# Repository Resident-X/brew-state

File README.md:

# `brew-state` — a model-based controller for a dual-thermoblock espresso machine

Replacing the factory control board in a Sunbeam EM7000 with a controller that actually models the machine: state estimation, a forward horizon, flow and pressure profiling, and a hardware safety chain with no firmware anywhere in it.

This repository is **public domain**. Take any of it.

## How this project is built

Requirements first, then code. The `specs/` graph is finished before firmware starts, and this repo is partly an argument that working in that order is faster rather than slower.

That means the graph is the substance here, and anything under `specs/` describes the machine as it is meant to be — not as it currently is.

## Where to start reading

**If you want to know what this machine is meant to do**, read the personas and journeys first. They are written to be read by a person, not parsed by a tool:

- `specs/personas/` — three stakeholders. The **operator** who makes coffee, the **builder** who designs and commissions it, and the **adopter** who found this published and owns a different machine.
- `specs/journeys/` — what actually happens: pulling a shot, steaming a jug, serving a group, commissioning the plant, correcting drift, keeping the machine in condition.

**If you want to know what constrains it**, read `specs/obligations/`. These are the cross-cutting commitments — electrical and thermal safety, real-time discipline, control-design discipline, verification discipline, open-source maintainability, physical configuration control. The safety obligation is the only one whose authority is external to this project, and it outranks everything else in the graph.

**If you want the detail**, `specs/requirements/` holds the functional and constraint requirements, `specs/definitions/` the vocabulary, and `specs/decisions/` the choices that have been made and why — including the options that were rejected.

**If you are rebuilding this on your own machine**, read [`docs/sunbeam-em7000/reference-machine.md`](docs/sunbeam-em7000/reference-machine.md) first. Everything specific to *our* machine — supply voltage, mains frequency, element ratings, protection trip points — lives in that one file. The requirement graph is written without those values so that replacing that file is the whole job.

## Two different promises

Be clear about which of these you are:

- **Same architecture** (a dual-thermoblock machine): the graph should apply to you, and adapting it should mean supplying your own parameters rather than changing requirements.
- **Different architecture** (single boiler, heat exchanger): the requirements will not all fit — an HX group's temperature depends on time since the last shot, which has no representation in a thermoblock's state at any parameter values. What transfers is the **method**, the tooling and the safety architecture. That is a smaller promise, and it is the honest one.

## Reading the graph

Nodes are `.req.yaml` files — plain YAML with prose in them. Reading needs nothing but a text editor. **Changing them is a different matter, and is covered below.**

**How they connect.** A requirement `derives-from` one or more *criteria* of the node above it, so the chain runs persona → journey → requirement, with each node carrying numbered criteria (`REQ-BREW-TEMP-001.C1`) attached by `criterion-of`. Obligations sit across the top: they are not part of that chain but constrain everything under them, and the safety obligation outranks the lot. Requirements also derive from each other's criteria where one genuinely builds on another. Decisions attach by `addresses`.

**Priorities.** Every requirement carries one:

| | |
|---|---|
| `must` | the system is wrong without it |
| `should` | real value, deliberately ranked below the musts |
| `could` | worth having, and shipping without it is not a defect |

Priority is about whether the system is wrong, not about when something gets built.

## Changing the graph

**Do not hand-edit `.req.yaml` files.** The graph is maintained by [Staircase](#staircase), and the engine is what holds it together: it assigns IDs, places files, wires and validates links, enforces the boundary between the requirement and delivery chains, applies the authoring discipline, and records who changed what and when.

Editing a node by hand bypasses all of that, and the failure mode is quiet. The file still parses. What breaks is underneath — a link pointing at something that no longer exists, a criterion orphaned from its parent, a requirement deriving from a retired one, a change landing with no version behind it and no event recording it. Structural validation does not catch most of that, because nothing is malformed. It is simply wrong, and it stays wrong until something downstream fails for reasons that no longer look connected.

That is the whole reason the engine exists. It is not a formatter over some YAML — it is the thing that knows how a systems and delivery graph has to hold together, so that a person changing one node does not have to.

**A caveat you should know before relying on this.** The engine is not part of this repository and is not currently something you can obtain. So you can read everything here, and you can build from it, but you cannot presently maintain a fork of the graph the way it is meant to be maintained. That is a real limit on what this repo currently offers, and it is tracked in the graph itself rather than hidden — `REQ-PUBLISHED-BUILD-PATH-001` requires every tool the path depends on to be obtainable by someone who is not the author, and that criterion is not met today.

## Staircase

This project is built with Staircase, whose thesis is that disciplined, requirement-driven, complete-the-first-time engineering produces better software, faster, that stays maintainable. This repo is partly a test of that claim in public, on a real physical thing that can burn someone.

One discipline is worth knowing about while reading: **requirements state properties, not mechanisms.** You will not find part numbers, sensor technologies, interface choices or tuning constants in `specs/`. Those are decisions and they live separately. That is also what makes the graph portable to a machine on a different continent running on a different voltage — a requirement that names a mechanism does not travel.

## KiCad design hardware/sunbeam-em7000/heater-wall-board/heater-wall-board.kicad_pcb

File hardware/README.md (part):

# Hardware

Board designs and the check every one of them has to pass before it is ordered.

- `hardware/<machine>/` holds one machine's board designs, one KiCad project per board in its own folder, and the `separation-basis.yaml`, `pin-allocation.yaml`, `controller-part.yaml`, `parts-specification.yaml`, `catalogue-extract.yaml` and `board-rules.yaml` they are held to, and the `derating-policy.yaml`, `pin-limits.yaml`, `workmanship-acceptance.yaml` and `severity-policy.yaml` they are held to where a design's folders hold them.
- `hardware/tools/` holds the pre-order check, the locked-copper check used around routing, the layout tools (the mains-copper compare beside it, the safe zone refill, the fill difference, the chain runner and the footprint audit), the command that renders a board's layout review views, the command that renders a placed board's placement view and measures it, the command that seeds the layout review's proof design, the review kit (the command that runs a declared judged review as forks of one shared context), the layout review's caller for it, the command that writes a committed board's review folder, the critical-routing check's caller and the catalogue helpers it shares with the layout caller, the production-files check's caller and the command that writes a real order's review folder, the schematic review's caller, the command that writes a committed schematic's review folder and the command that proves the fanned-out schematic review (with the proof harness it shares with the layout review's), the command that proves the fanned-out layout review, the commands that convert and draw a board's production files and the command that seeds the proof design's production files, and their tests. They work for any machine.
- `hardware/proof/` holds designs committed only to prove the board tooling and the layout review: `gate-proof` for the pre-order check's rules, `record-keys-proof` for the keys its records carry, `review-proof` for the layout review and the ordering step's production-files check, and `circuit-review-proof` for the schematic review. They are never ordered.

A **board design** is a KiCad project file (`.kicad_pro`) together with the schematic (`.kicad_sch`) and layout (`.kicad_pcb`) of the same name beside it. The check finds every design git tracks, wherever it sits. The layout above is a convention for readers, not something the check depends on. A design is checked once git tracks it: `git add` is enough for the design's own files. The check reads a design only as the repository holds it. KiCad is given a copy of the tracked files alone, each in its place in the repository: everything in the design's folder, every sheet its schematic reaches, and every library its `sym-lib-table` and `fp-lib-table` name, wherever in the repository they sit. A library, sheet or rules file left uncommitted is therefore not used. A sheet the schematic names, a custom rules file or library table beside the project, or a library a table names, that git does not track fails the design by name. So does a library the repository cannot hold at all: one named by an absolute path, one outside the repository, or one reached through a path variable other than `${KIPRJMOD}` and those naming the libraries KiCad installs with itself (`${KICAD10_SYMBOL_DIR}`, `${KICAD10_FOOTPRINT_DIR}` and the like). Name a library from its table as `${KIPRJMOD}/` followed by its path from the design's folder. The separation basis record has to be committed exactly as it stands (see below).

KiCad is run with a configuration the check makes for the run, not the one on the machine running it. That configuration names only the libraries KiCad installs with itself, and no `KICAD…` variable from the environment reaches KiCad. A symbol or footprint whose library only one machine's own KiCad setup names, in its global library tables or its path variables, is therefore reported by KiCad as a library its configuration does not include, and fails the design under `design_library`. Put such a library in the repository and name it in the design's own table.

One KiCad run may take at most 7200 s. The limit is the constant `KICAD_TIMEOUT_S` in `hardware/tools/board_check.py`, and `hardware/tools/board_views.py` reads the same constant, so neither tool has a figure of its own. A run that outlives it fails the design as "KiCad did not finish within 7200 s", with the limit in force named, in the check and in the views command; the wait is finite, so a hung run still fails. The figure rests on a measurement made on 2026-10-31 on the main board with its ground and neutral pours and slots: KiCad's creepage test alone took about 10 minutes and the full design check 20 to 30 minutes; a later measurement on the main board as it was laid out found one full-board KiCad pass taking about 50 minutes, nearly all of it the creepage test against the ground pours, and the check makes that pass once (the mounting-hole and sensing passes hold no creepage constraint). 7200 s is about four times the slowest of the first measurements and more than twice the single pass measured later, the margin that lets a slower machine or a denser board finish.

## What you need

Every tool is free. The check stops with an error naming any tool that is missing or too old, rather than skipping the checks that need it.

| Tool | Minimum | Where to get it |
|---|---|---|
| KiCad (its `kicad-cli`) | KiCad 10.0 | https://www.kicad.org/download/. This repository's board files are in KiCad 10's format, which older versions cannot open. |
| Python | Python 3.9 | https://www.python.org/downloads/ |
| PyYAML | PyYAML 5.1 | `pip install pyyaml`, or your system's `python3-yaml` package |
| git | git 2.11 | https://git-scm.com/downloads |
| Task | 3 | https://taskfile.dev/installation/ |
| resvg, for the layout review views and for the tooling tests the build round runs | resvg 0.47 | A prebuilt program from https://github.com/linebender/resvg/releases: the v0.47.0 release carries one for each of Windows (`resvg-win64.zip`), macOS and Linux (x86_64), and later releases carry them for macOS and Linux only. Or `brew install resvg` with Homebrew, on macOS or Linux. Or `cargo install resvg` with a Rust toolchain from https://rustup.rs/, on any operating system. It turns the views into images. The pre-order check itself does not need it, but the tooling tests that the build round and the nightly run draw views, so those need it too ([When the board check runs](#when-the-board-check-runs)). |
| gerbonara, for the commands that draw a board's exported fabrication layers and for the tooling tests the build round runs | gerbonara 1.6.3, exactly | A Python library under the Apache licence, https://pypi.org/project/gerbonara/. Install it into a virtual environment of its own with `task hw:gerbonara`, which makes one in your user cache folder (`GERBONARA_VENV` puts it elsewhere), or by hand with `python3 -m venv <folder>` then `<folder>/bin/python -m pip install gerbonara==1.6.3` (on Windows `<folder>\Scripts\python.exe`) and name that environment's Python as `GERBONARA_PYTHON`. It reads the Gerber and drill files KiCad exports, which `kicad-cli` cannot, and the ordering step of the method turns each into a vector image that resvg rasterises. The pre-order check itself does not need it, but the tooling tests that the build round and the nightly run draw layers from exported files, so those need it too. A command or a test that needs it and does not find that version stops with `CANNOT RUN` naming it. |
| KiCad's own Python, for the layout tools that run KiCad's scripting interface (the zone refill, the fill difference and any chain step that loads a board) | the interpreter that ships with KiCad 10.0 | It is part of the KiCad install: the one interpreter that can `import pcbnew`. Name it with the environment variable `KICAD_PYTHON`, or with the tool's `--kicad-python` argument, which wins. A tool and its tests that need it stop with `CANNOT RUN` naming `KICAD_PYTHON` when it is unset or names nothing runnable. Check it with `"$KICAD_PYTHON" -c "import pcbnew; print(pcbnew.Version())"`. Its usual location is in the table below. `task hw:test` and `task hw:test:round` find it as they find `KICAD_CLI`: the variable when set, else the macOS install's interpreter when it is there, else the system `python3` when that can import `pcbnew`, else nothing, and the tests that need it stop naming it. The nightly verification's runner sets it, and `KICAD_FOOTPRINTS`, in a step that fails the provisioning when `/usr/bin/python3` cannot import `pcbnew`. |
| numpy, shapely, Pillow and PyYAML, for the silkscreen command (`silkscreen.py build`, `check` and `prove`) and the tests of it | numpy 2.5.0, shapely 2.2.0, Pillow 12.3.0 and PyYAML 6.0.3, or later | Python libraries. Install them into a virtual environment of their own with `task hw:silkscreen`, which makes one in your user cache folder (`SILKSCREEN_VENV` puts it elsewhere), or into the Python that runs the command by hand (`pip install numpy shapely Pillow pyyaml`, or your system's `python3-numpy`, `python3-shapely`, `python3-pil` and `python3-yaml` packages). The rest of the board tooling does not need them, and no tool here carries a copy of them. A command or test that needs one and does not find it stops with `CANNOT RUN` naming the package. |
| A monospaced font for the captions, for the layout review views and for the tooling tests the build round runs | DejaVu Sans Mono, or Menlo, Consolas, Liberation Mono or Courier New | The captions are drawn in the first of these that resvg finds among the system's fonts. macOS carries Menlo and Windows carries Consolas. Elsewhere, install DejaVu Sans Mono from https://dejavu-fonts.github.io/ or your system's package of it (for example `fonts-dejavu`). Without one the command, or the tooling tests, stop with `CANNOT RUN`. |

`kicad-cli` is often installed off the search path. The tasks use the variable `KICAD_CLI`, which defaults to the bare name `kicad-cli`. If it is not on your search path, set the variable to the tool's full path, either on the command line (`task hw:verify KICAD_CLI=/path/to/kicad-cli`) or in the environment. Its usual location:

| System | `kicad-cli` |
|---|---|
| macOS | `/Applications/KiCad/KiCad.app/Contents/MacOS/kicad-cli` |
| Windows | `C:\Program Files\KiCad\10.0\bin\kicad-cli.exe` |
| Linux (distribution or PPA package) | `/usr/bin/kicad-cli` |
| Linux (Flatpak) | not a file on the path: write a one-line script that runs `flatpak run --command=kicad-cli org.kicad.KiCad "$@"` and point `KICAD_CLI` at it |

KiCad's stock footprint libraries are needed by the main board's layout chain only when a block must take a part from them that the board does not carry (a part swap or a clamp it adds); the chain stops with `KICAD_FOOTPRINTS must name KiCad's stock footprint libraries ...` naming the variable when that happens and the variable is unset or names no folder. Name the folder that holds `Capacitor_SMD.pretty` and the other `.pretty` folders with `KICAD_FOOTPRINTS`: on macOS `/Applications/KiCad/KiCad.app/Contents/SharedSupport/footprints`, on Windows `C:\Program Files\KiCad\10.0\share\kicad\footprints`, on Linux `/usr/share/kicad/footprints`. Running the chain over the committed main board needs no part from them. The same two tasks pass `KICAD_FOOTPRINTS` on, taking the variable when set and else the first of the macOS and Linux places above that exists.

KiCad's own Python is, on each system, usually:

| System | `KICAD_PYTHON` |
|---|---|
| macOS | `/Applications/KiCad/KiCad.app/Contents/Frameworks/Python.framework/Versions/Current/bin/python3` |
| Windows | `C:\Program Files\KiCad\10.0\bin\python.exe` |
| Linux (distribution or PPA package) | `/usr/bin/python3`, which imports `pcbnew` once the `kicad` package is installed |
| Linux (Flatpak) | not a file on the path: write a one-line script that runs `flatpak run --command=python3 org.kicad.KiCad "$@"` and point `KICAD_PYTHON` at it |

`SILKSCREEN_PYTHON` is the Python of the silkscreen libraries' environment (`task hw:silkscreen`, pinned to numpy 2.5.0, shapely 2.2.0, Pillow 12.3.0 and PyYAML 6.0.3, which the command's table needs, safe to run again). It defaults to the Python of that environment once it exists and to `python3` when there is none. The silkscreen command and its tests start in whatever Python runs them; when that lacks one of the three packages and `SILKSCREEN_PYTHON` names a Python that has all three, they run again under it, so a bare `python3` works. When neither has them, the command stops with `CANNOT RUN` naming the missing package, the task and the variable. `task hw:test` and `task hw:test:round` pass the variable to the tests, and the nightly run installs the same pinned versions into its own environment and sets it.

`GERBONARA_PYTHON` is the Python of the virtual environment above. The tasks that draw layers use the variable, which defaults to the Python of the environment `task hw:gerbonara` makes and to `python3` when there is none, so only an environment made by hand needs it set, on the command line (`task hw:production-seed GERBONARA_PYTHON=/path/to/venv/bin/python -- ...`) or in the environment.

`resvg` is one program, wherever it was unpacked. The view tasks use the variable `RESVG`, which defaults to the bare name `resvg`. If it is not on your search path, set it to the program's full path, for example `task hw:views RESVG=/path/to/resvg -- ...`.

## The commands

- `task hw:verify` runs the pre-order check on every board design in the repository. It exits 0 only when every design passes. A build round runs it for a change that can matter to a board, and the nightly run of `main` runs it every night ([When the board check runs](#when-the-board-check-runs)).
- `task hw:prove` seeds each fault the check guards against into a throwaway copy of `hardware/proof/gate-proof` (or, for a fault about the keys of a record, of `hardware/proof/record-keys-proof`, for a fault about an unlisted pin of `hardware/proof/circuit-review-proof`, and for a fault about sensing clearance or ground returns of `hardware/proof/review-proof`) as the last commit holds it, in a temporary directory outside the repository, so an uncommitted edit to the proof design is not what it proves. It requires the check to catch each fault. This command is on demand: neither the build round nor the nightly runs it.
- `task hw:review-seed -- --seeds <file> --out <folder>` seeds known layout defects into a throwaway copy of `hardware/proof/review-proof` and writes a folder to review it blind, with the seed list apart (see [The proof designs](#the-proof-designs)). This command is on demand and is not part of the gate. It needs the same tools as `hw:views`.
- `task hw:production-review-folder -- --repo <repository> --commit <commit> --design <board folder> --out <folder> --work <folder> --views <folder> --placement <folder> --preview <folder> --preview-note <text> --tools <text> --command <text> ...` writes the review folder of a real order's production-files check for a judged review to read ([The production-files check by unit](#the-production-files-check-by-unit)). This command is on demand and is not part of the gate. It needs git and Python, no KiCad and no gerbonara.
- `task hw:production-seed -- --seeds <file> --out <folder>` seeds known defects into the production files of `hardware/proof/review-proof` and writes a folder to check them blind, with the seed list apart (see [The proof designs](#the-proof-designs)). This command is on demand and is not part of the gate. It needs the same tools as `hw:views`, and gerbonara.
- `task hw:test` runs the tests of the check itself, of the locked-copper check's four commands, of the layout review views, of the placement view, of the placement and critical routing history check, of the layout review record history check, of the layout review proof's seeding command, of the schematic sheet drawing command, of the review kit (its session specification and executors, answer reading, stream checks and telemetry, declaration, catalogue and shared context, planner and scheduler, merge and replicas, caller contract, contract smoke, the command and the task runner's file), of the layout review's caller, the critical-routing check's caller and the shared catalogue helpers, the production-files check's caller and its folder command, the schematic review's caller, the schematic review folder command and the schematic review proof command, the review folder command, the layout review proof command, the critical-routing review proof command and the production-files review proof command, and of the production-files conversion, rendering and seeding commands, against the real `kicad-cli`, `resvg` and gerbonara. It includes the tests that run the seeded-fault proof, so it is the whole suite, on demand.
- `task hw:test:round` runs the same tests without those that need the seeded-fault proof. It is the tooling-test part of the build round's board tier and of the nightly run ([When the board check runs](#when-the-board-check-runs)). It needs the same tools as `hw:test`: KiCad, resvg, a monospaced font and gerbonara.
  Both tasks run each test file in a process of its own, side by side, through `firmware/tools/run_tool_tests.py` (the runner the firmware tooling's tests use), from the repository root as a serial discovery run does. The runner fails when it finds no test file, names every file that fails, and writes a missing tool's `CANNOT RUN |` line once to its error output so the round reads it as a failure to look. The stage runs at most four files at once unless asked for more (`task hw:test -- --workers 10`), because the machine running the round is shared with other sessions; `task hw:test -- --workers 1` runs the files one after another. The long test files are divided by topic so no one file holds the stage: the KiCad check's tests into `test_board_check_kicad_*.py` (their shared setup and the exclusion of the seeded-fault proof in `board_kicad_fixtures.py`), the layout review views' into `test_board_views_*.py`, the history check's into `test_board_history_*.py`, the locked-copper check's into `test_locked_copper_*.py` and the review proof design's rules into `test_review_proof_rules_*.py`, each with its shared setup in a `*_fixtures.py` beside them; `test_board_kicad_division.py` holds each division to the tests the undivided file held, each in exactly one file. A test class whose tests only read a copy of a proof design and the result of checking it derives from `SharedCopy` and makes the copy and the check once, with the copy fingerprinted and verified unchanged after each test; a test that changes its copy derives from `Copy` and has one of its own.
- `task hw:reads` lists, one per line, every file the board designs git tracks read: each design's folder (with a trailing slash), its sheets, its libraries and the separation basis, pin allocation, controller part, parts specification, catalogue extract, derating policy, pin-limit, board rules and manufacturer limits records it is held to. It runs no check and needs only git and Python, no KiCad. The build round asks it which changed paths reach a board design.
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
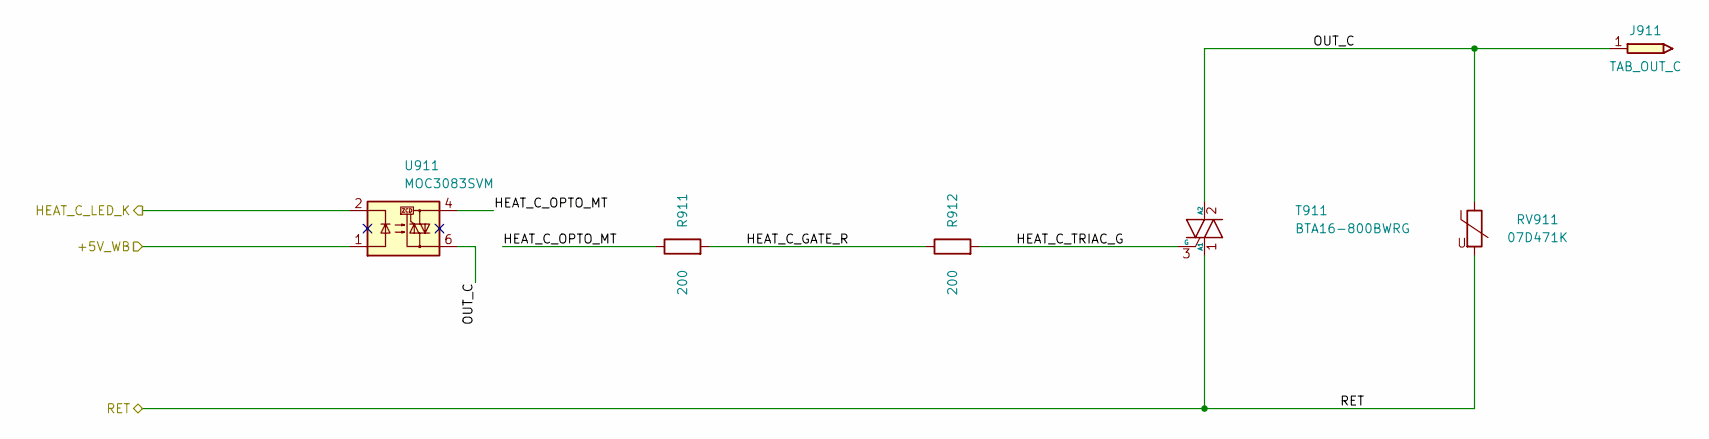
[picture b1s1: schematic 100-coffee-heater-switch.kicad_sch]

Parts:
J911: TAB_OUT_C; Tab_TE_63849-1; Rating 6.3 x 0.8 mm blade, board-mounted PC ta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; MPN 63849-1; LCSC C86469
R911, R912: 200; R_1206_3216Metric; Rating 1% 250mW RCWV 7.07V 1206; MPN 1206W4F2000T5E; LCSC C18002
RV911: 07D471K; RV_Disc_D9mm_W5.2mm_P5mm; Rating 07D471K 470 V disc varistor, 5 mm lead 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; MPN 07D471K; LCSC C49072860
T911: BTA16-800BWRG; TO-220-3_Vertical_Insulated_OvalPads; Rating 800 V 16 A insulated TO-220AB snubberle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; MPN BTA16-800BWRG; LCSC C10065
U911: MOC3083SVM; SMDIP-6_W9.53mm_MOC3083SR2M; Rating 800 V zero-cross opto-triac driver, MOC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; MPN MOC3083SVM; LCSC C899868

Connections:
/+5V_WB: U911.1; also elsewhere on the board
/Coffee heater switch/HEAT_C_GATE_R: R911.2, R912.1
/Coffee heater switch/HEAT_C_OPTO_MT: R911.1, U911.4
/Coffee heater switch/HEAT_C_TRIAC_G: R912.2, T911.3 (G)
/Coffee heater switch/OUT_C: J911.1, RV911.1, T911.2 (A2), U911.6
/HEAT_C_LED_K: U911.2; also elsewhere on the board
/RET: RV911.2, T911.1 (A1); also elsewhere on the board

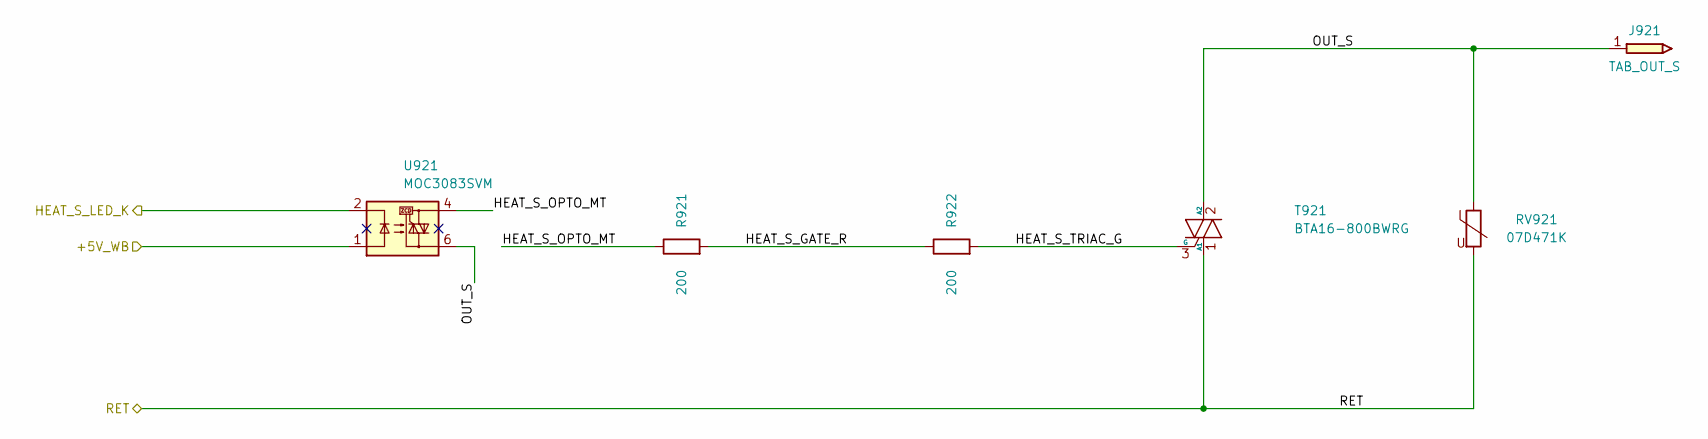
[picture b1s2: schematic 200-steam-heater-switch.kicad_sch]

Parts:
J921: TAB_OUT_S; Tab_TE_63849-1; Rating 6.3 x 0.8 mm blade, board-mounted PC ta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; MPN 63849-1; LCSC C86469
R921, R922: 200; R_1206_3216Metric; Rating 1% 250mW RCWV 7.07V 1206; MPN 1206W4F2000T5E; LCSC C18002
RV921: 07D471K; RV_Disc_D9mm_W5.2mm_P5mm; Rating 07D471K 470 V disc varistor, 5 mm lead 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; MPN 07D471K; LCSC C49072860
T921: BTA16-800BWRG; TO-220-3_Vertical_Insulated_OvalPads; Rating 800 V 16 A insulated TO-220AB snubberle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; MPN BTA16-800BWRG; LCSC C10065
U921: MOC3083SVM; SMDIP-6_W9.53mm_MOC3083SR2M; Rating 800 V zero-cross opto-triac driver, MOC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; MPN MOC3083SVM; LCSC C899868

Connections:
/+5V_WB: U921.1; also elsewhere on the board
/HEAT_S_LED_K: U921.2; also elsewhere on the board
/RET: RV921.2, T921.1 (A1); also elsewhere on the board
/Steam heater switch/HEAT_S_GATE_R: R921.2, R922.1
/Steam heater switch/HEAT_S_OPTO_MT: R921.1, U921.4
/Steam heater switch/HEAT_S_TRIAC_G: R922.2, T921.3 (G)
/Steam heater switch/OUT_S: J921.1, RV921.1, T921.2 (A2), U921.6

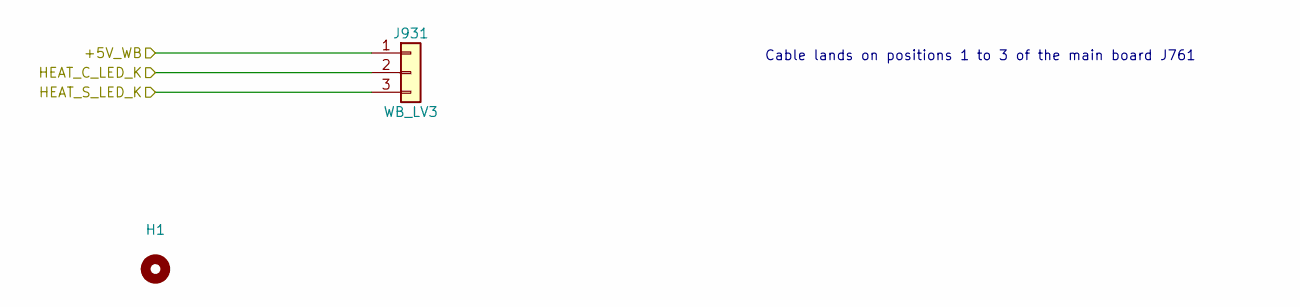
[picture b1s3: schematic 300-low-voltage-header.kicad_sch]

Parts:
H1: MountingHole; MountingHole_3.2mm_M3; Rating M3 screw, 3.2 mm non-plated hole; LCSC none
J931: WB_LV3; PinHeader_1x03_P2.54mm_Vertical; Rating 1x3 2.54 mm pin header, 3 A, vertical; MPN PZ254V-11-03P; LCSC C2937625

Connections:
/+5V_WB: J931.1; also elsewhere on the board
/HEAT_C_LED_K: J931.2; also elsewhere on the board
/HEAT_S_LED_K: J931.3; also elsewhere on the board

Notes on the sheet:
Cable lands on positions 1 to 3 of the main board J761

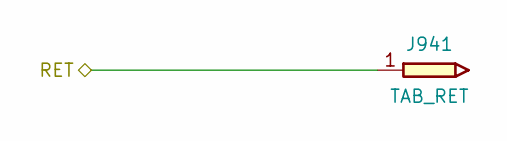
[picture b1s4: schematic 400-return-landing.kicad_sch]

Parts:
J941: TAB_RET; Tab_TE_63849-1; Rating 6.3 x 0.8 mm blade, board-mounted PC ta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; MPN 63849-1; LCSC C86469

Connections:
/RET: J941.1; also elsewhere on the board

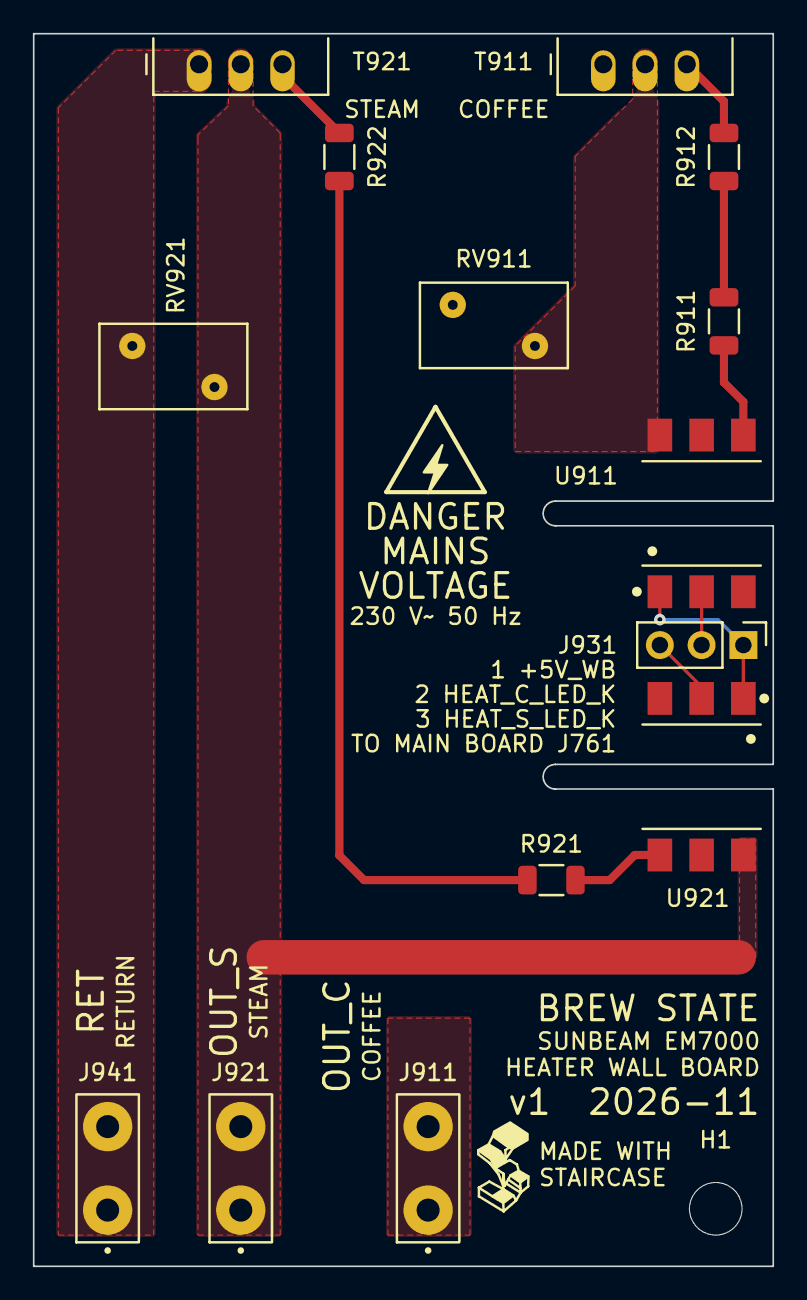
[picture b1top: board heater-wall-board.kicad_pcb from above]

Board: 2 copper layers, 45.0 x 75.0 mm, 15 parts (0 on the bottom side), 12 nets.

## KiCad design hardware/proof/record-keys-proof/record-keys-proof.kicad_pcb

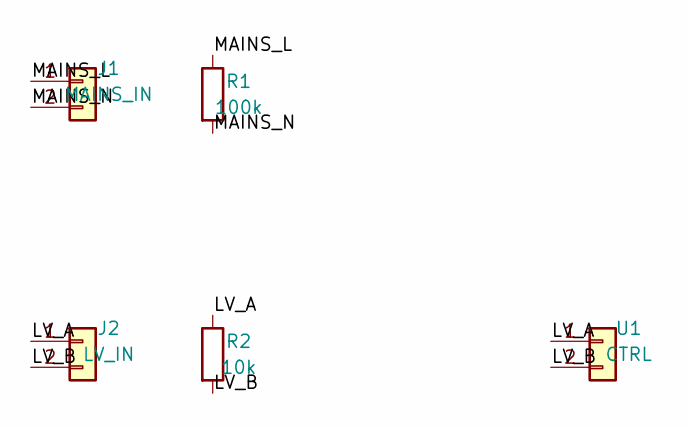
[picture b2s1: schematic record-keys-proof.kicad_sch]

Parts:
J1: MAINS_IN; PinHeader_1x02_P2.54mm_Vertical; LCSC C9000001
J2: LV_IN; PinHeader_1x02_P2.54mm_Vertical; LCSC C9000003
R1: 100k; R_Axial_DIN0207_L6.3mm_D2.5mm_P10.16mm_Horizontal; Rating 0.25W; LCSC C9000002
R2: 10k; R_Axial_DIN0207_L6.3mm_D2.5mm_P10.16mm_Horizontal; Rating 0.25W; LCSC C9000004
U1: CTRL; Controller_1x02; LCSC C9000005

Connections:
/LV_A: J2.1, R2.1, U1.1 (PA0)
/LV_B: J2.2, R2.2, U1.2 (PA1)
/MAINS_L: J1.1, R1.1
/MAINS_N: J1.2, R1.2

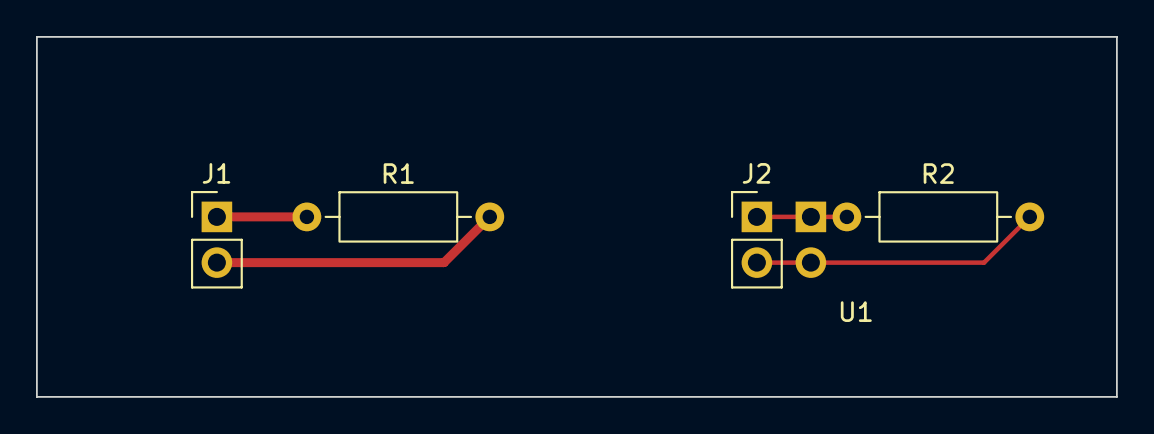
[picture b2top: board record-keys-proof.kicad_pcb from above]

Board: 2 copper layers, 60.0 x 20.0 mm, 5 parts (0 on the bottom side), 4 nets.

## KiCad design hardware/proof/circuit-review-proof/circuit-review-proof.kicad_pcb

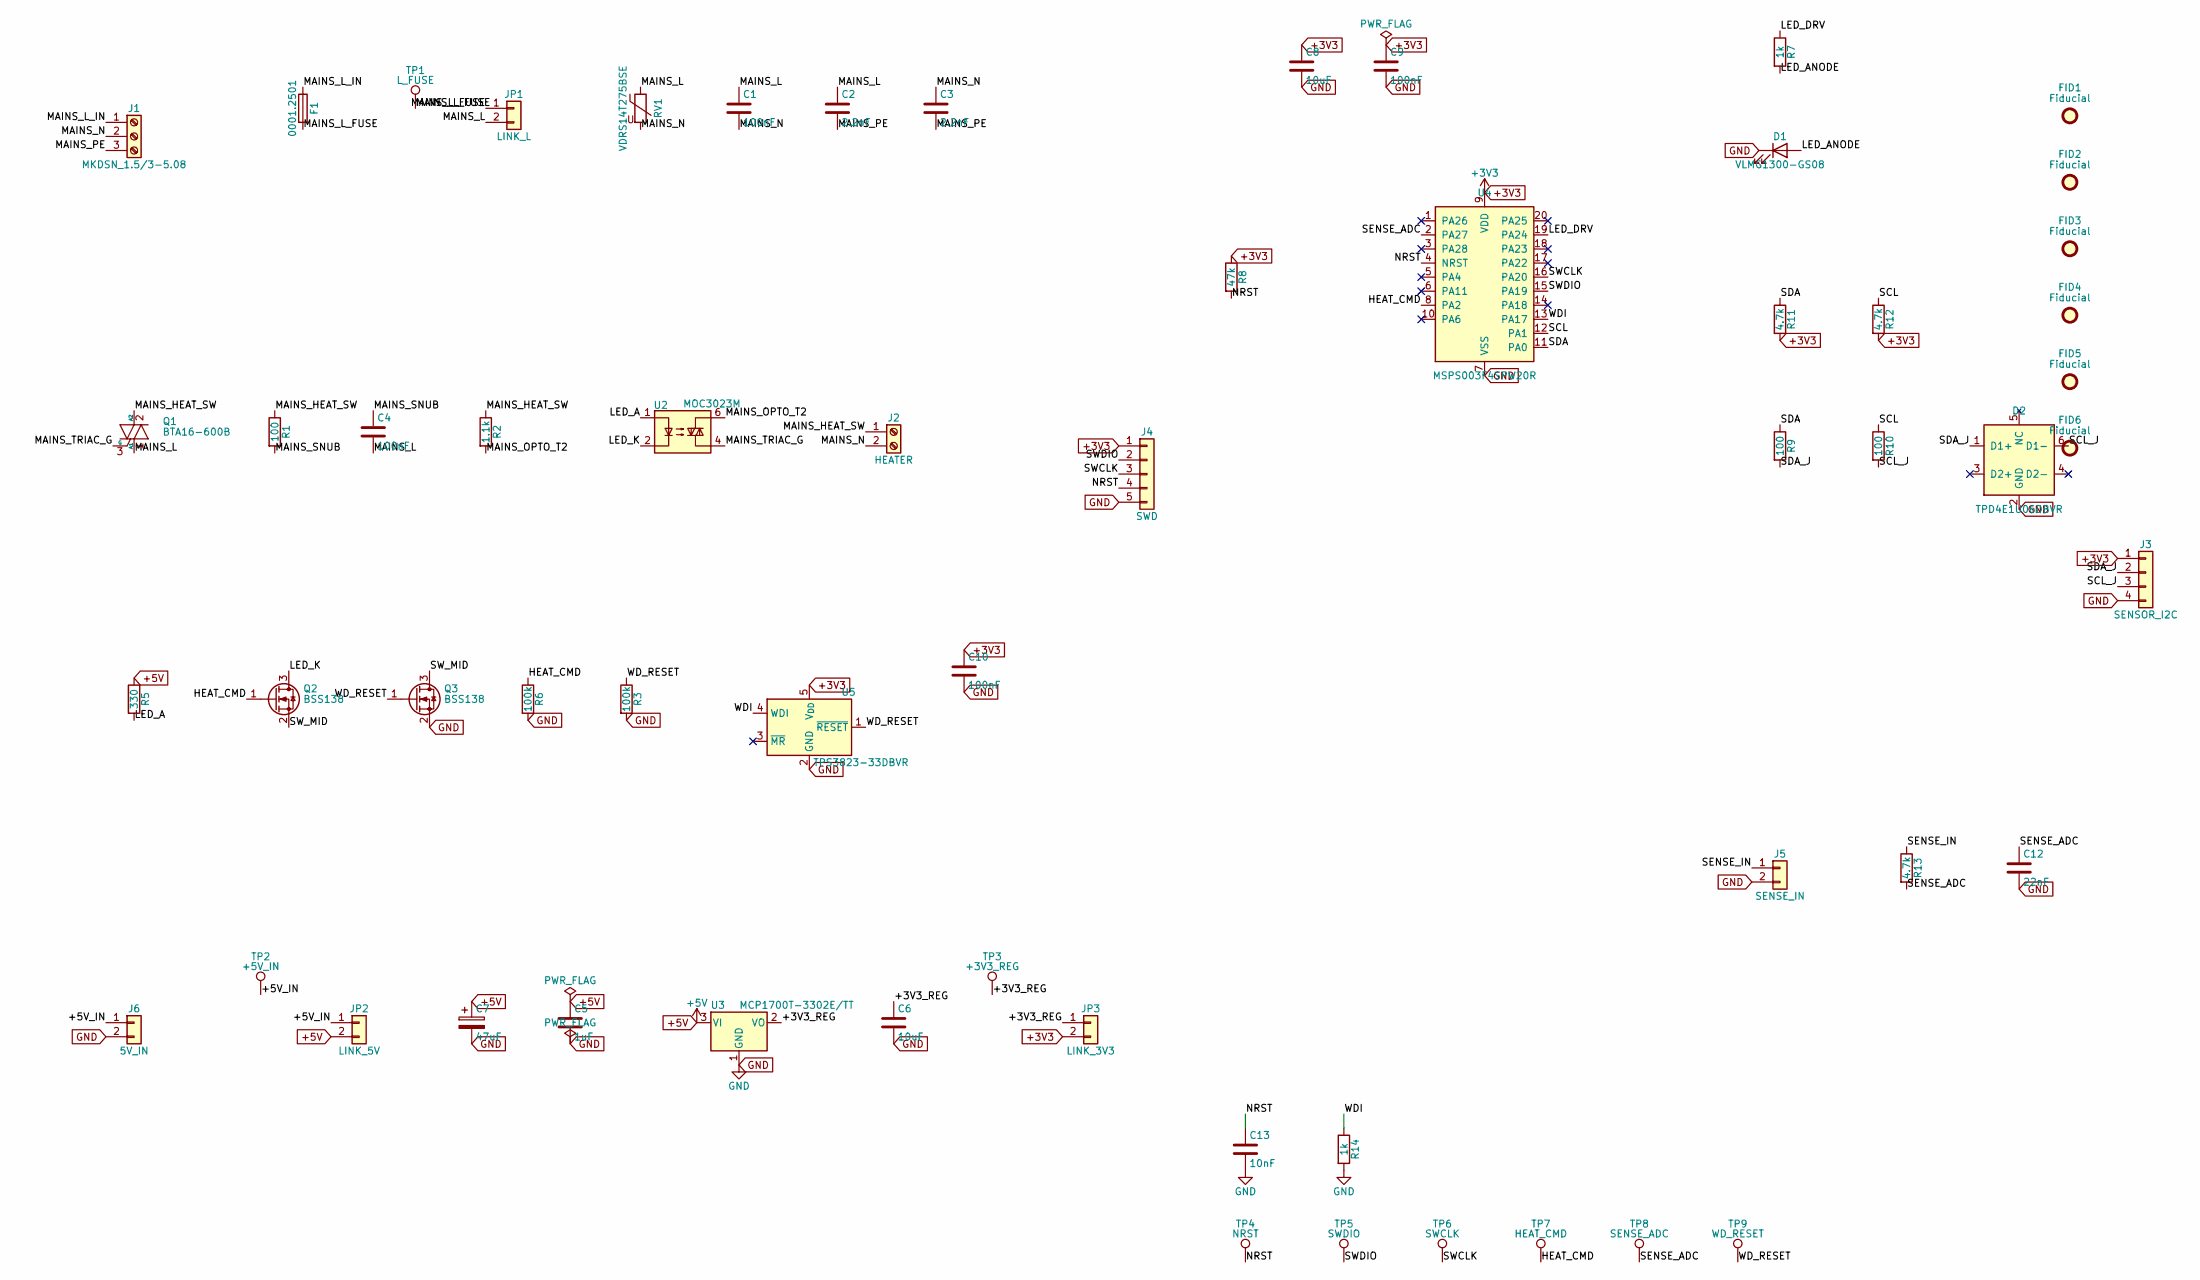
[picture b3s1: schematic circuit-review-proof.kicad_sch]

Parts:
C1, C4: 100nF; C_Rect_L18.0mm_W7.0mm_P15.00mm_FKS3_FKP3; Rating 275VAC; LCSC C9200007
C2, C3: 2.2nF; C_Disc_D7.0mm_W2.5mm_P5.00mm; Rating 250VAC; LCSC C9200008
C5: 1uF; C_0603_1608Metric; Rating 16V; LCSC C9200029
C6, C8: 10uF; C_0805_2012Metric; Rating 10V; LCSC C9200031
C7: 47uF; CP_EIA-3528-21_Kemet-B; Rating 10V; LCSC C9200028
C9, C10: 100nF; C_0603_1608Metric; Rating 16V; LCSC C9200021
C12: 22nF; C_0603_1608Metric; Rating 16V; LCSC C9200037
C13: 10nF; C_0603_1608Metric; Rating 16V; LCSC C9200036
D1: VLMG1300-GS08; LED_0603_1608Metric; Rating 30mA; LCSC C9200034
D2: TPD4E1U06DBVR; SOT-23-6; Rating 5.5V; LCSC C9200035
F1: 0001.2501; Fuseholder_Cylinder-5x20mm_Bulgin_FX0457_Horizontal_Closed; Rating 500mA 250VAC; LCSC C9200003
FID1, FID2, FID3, FID4, FID5, FID6: Fiducial; Fiducial_1mm_Mask2mm; LCSC C9200038
J1: MKDSN_1.5/3-5.08; TerminalBlock_Phoenix_MKDS-1,5-3-5.08_1x03_P5.08mm_Horizont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; Rating 320VAC 8A; LCSC C9200001
J2: HEATER; TerminalBlock_Phoenix_MKDS-1,5-2-5.08_1x02_P5.08mm_Horizont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; Rating 320VAC 8A; LCSC C9200002
J3: SENSOR_I2C; JST_XH_B4B-XH-A_1x04_P2.50mm_Vertical; Rating 3A 250V; LCSC C9200025
J4: SWD; PinHeader_1x05_P2.54mm_Vertical; Rating 3A; LCSC C9200033
J5: SENSE_IN; JST_XH_B2B-XH-A_1x02_P2.50mm_Vertical; Rating 3A 250V; LCSC C9200024
J6: 5V_IN; JST_XH_B2B-XH-A_1x02_P2.50mm_Vertical; Rating 3A 250V; LCSC C9200023
JP1: LINK_L; SolderWire-1sqmm_1x02_P7.8mm_D1.4mm_OD3.9mm; Rating 300VAC 6A; LCSC C9200005
JP2: LINK_5V; PinHeader_1x02_P2.54mm_Vertical; Rating 3A; LCSC C9200026
JP3: LINK_3V3; PinHeader_1x02_P2.54mm_Vertical; Rating 3A; LCSC C9200027
Q1: BTA16-600B; TO-220-3_Vertical; Rating 600V 16A; LCSC C9200009
Q2, Q3: BSS138; SOT-23; Rating 50V 0.22A; LCSC C9200014
R1: 100; R_2512_6332Metric; Rating 1W; LCSC C9200010
R2: 1.1k; R_1206_3216Metric; Rating 0.25W; LCSC C9200011
R3, R6: 100k; R_0603_1608Metric; Rating 0.1W; LCSC C9200015
R5: 330; R_1206_3216Metric; Rating 0.25W; LCSC C9200013
R7, R14: 1k; R_0603_1608Metric; Rating 0.1W; LCSC C9200017
R8: 47k; R_0603_1608Metric; Rating 0.1W; LCSC C9200016
R9, R10: 100; R_0603_1608Metric; Rating 0.1W; LCSC C9200018
R11, R12, R13: 4.7k; R_0603_1608Metric; Rating 0.1W; LCSC C9200019
RV1: VDRS14T275BSE; RV_Disc_D15.5mm_W5.4mm_P7.5mm; Rating 275VAC; LCSC C9200006
TP1: L_FUSE; TestPoint_Pad_D1.0mm; Rating 1A; LCSC C9200004
TP2: +5V_IN; TestPoint_Pad_D1.0mm; Rating 1A; LCSC C9200004
TP3: +3V3_REG; TestPoint_Pad_D1.0mm; Rating 1A; LCSC C9200004
TP4: NRST; TestPoint_Pad_D1.0mm; Rating 1A; LCSC C9200004
TP5: SWDIO; TestPoint_Pad_D1.0mm; Rating 1A; LCSC C9200004
TP6: SWCLK; TestPoint_Pad_D1.0mm; Rating 1A; LCSC C9200004
TP7: HEAT_CMD; TestPoint_Pad_D1.0mm; Rating 1A; LCSC C9200004
TP8: SENSE_ADC; TestPoint_Pad_D1.0mm; Rating 1A; LCSC C9200004
TP9: WD_RESET; TestPoint_Pad_D1.0mm; Rating 1A; LCSC C9200004
U2: MOC3023M; DIP-6_W7.62mm; Rating 400V; LCSC C9200012
U3: MCP1700T-3302E/TT; SOT-23; Rating 6V; LCSC C9200030
U4: MSPS003F4SPW20R; TSSOP-20_4.4x6.5mm_P0.65mm; Rating 4.1V; LCSC C9200032
U5: TPS3823-33DBVR; SOT-23-5; Rating 6V; LCSC C9200020

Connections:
/+3V3_REG: C6.1, JP3.1, TP3.1, U3.2 (VO)
/+5V_IN: J6.1, JP2.1, TP2.1
/HEAT_CMD: Q2.1 (G), R6.1, TP7.1, U4.8 (PA2)
/LED_A: R5.2, U2.1
/LED_ANODE: D1.2 (A), R7.2
/LED_DRV: R7.1, U4.19 (PA24)
/LED_K: Q2.3 (D), U2.2
/MAINS_HEAT_SW: J2.1, Q1.2 (A2), R1.1, R2.1
/MAINS_L: C1.1, C2.1, C4.2, JP1.2, Q1.1 (A1), RV1.1
/MAINS_L_FUSE: F1.2, JP1.1, TP1.1
/MAINS_L_IN: F1.1, J1.1
/MAINS_N: C1.2, C3.1, J1.2, J2.2, RV1.2
/MAINS_OPTO_T2: R2.2, U2.6
/MAINS_PE: C2.2, C3.2, J1.3
/MAINS_SNUB: C4.1, R1.2
/MAINS_TRIAC_G: Q1.3 (G), U2.4
/NRST: C13.1, J4.4, R8.2, TP4.1, U4.4 (NRST)
/SCL: R10.1, R12.1, U4.12 (PA1)
/SCL_J: D2.6 (D1-), J3.3, R10.2
/SDA: R9.1, R11.1, U4.11 (PA0)
/SDA_J: D2.1 (D1+), J3.2, R9.2
/SENSE_ADC: C12.1, R13.2, TP8.1, U4.2 (PA27)
/SENSE_IN: J5.1, R13.1
/SWCLK: J4.3, TP6.1, U4.16 (PA20)
/SWDIO: J4.2, TP5.1, U4.15 (PA19)
/SW_MID: Q2.2 (S), Q3.3 (D)
/WDI: R14.1, U4.13 (PA17), U5.4 (WDI)
/WD_RESET: Q3.1 (G), R3.1, TP9.1, U5.1 (~RESET)

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
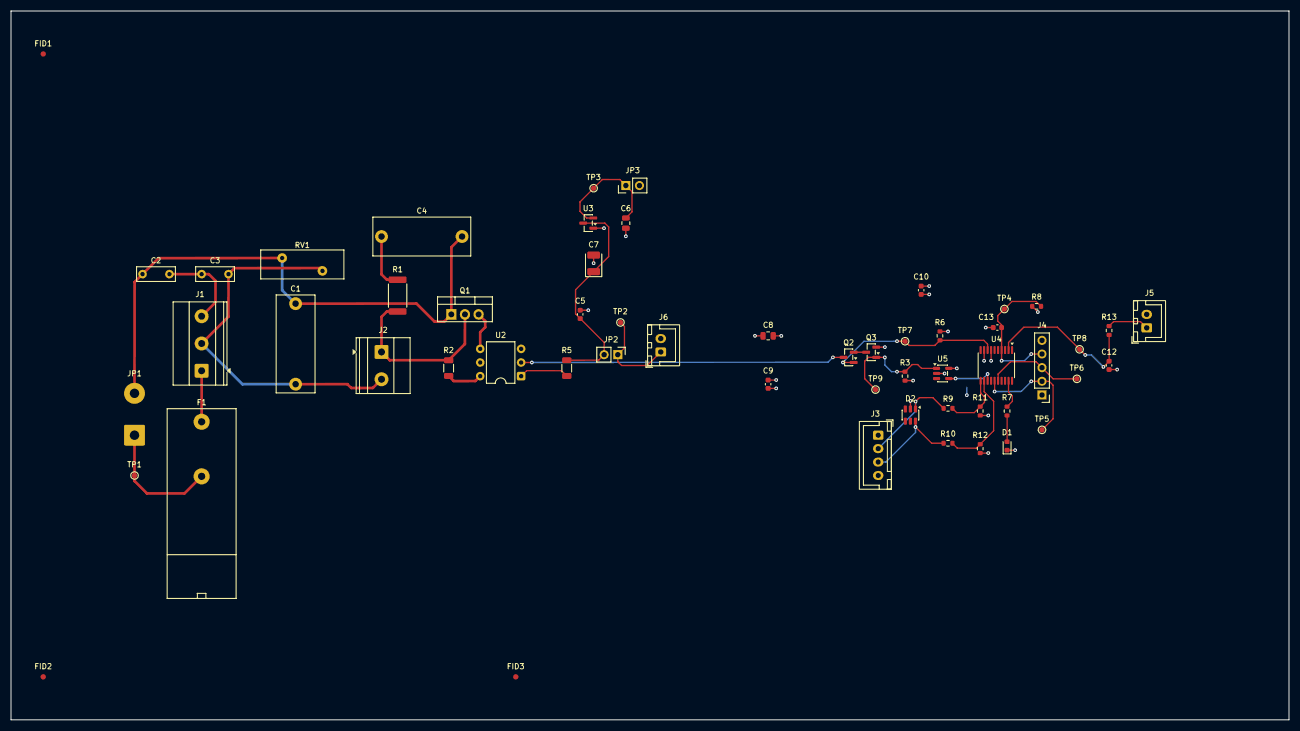
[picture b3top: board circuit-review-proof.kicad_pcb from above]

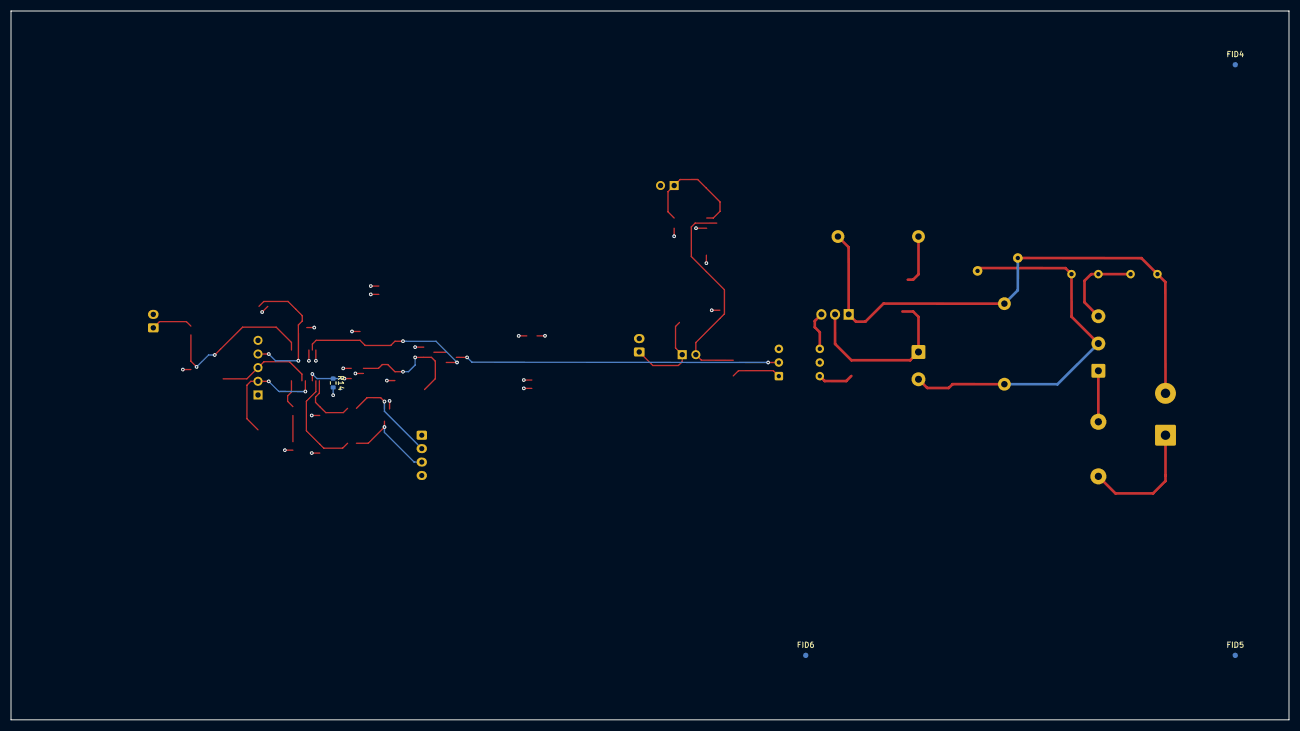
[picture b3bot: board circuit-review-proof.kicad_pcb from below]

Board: 4 copper layers, 238.0 x 132.0 mm, 60 parts (4 on the bottom side), 31 nets.

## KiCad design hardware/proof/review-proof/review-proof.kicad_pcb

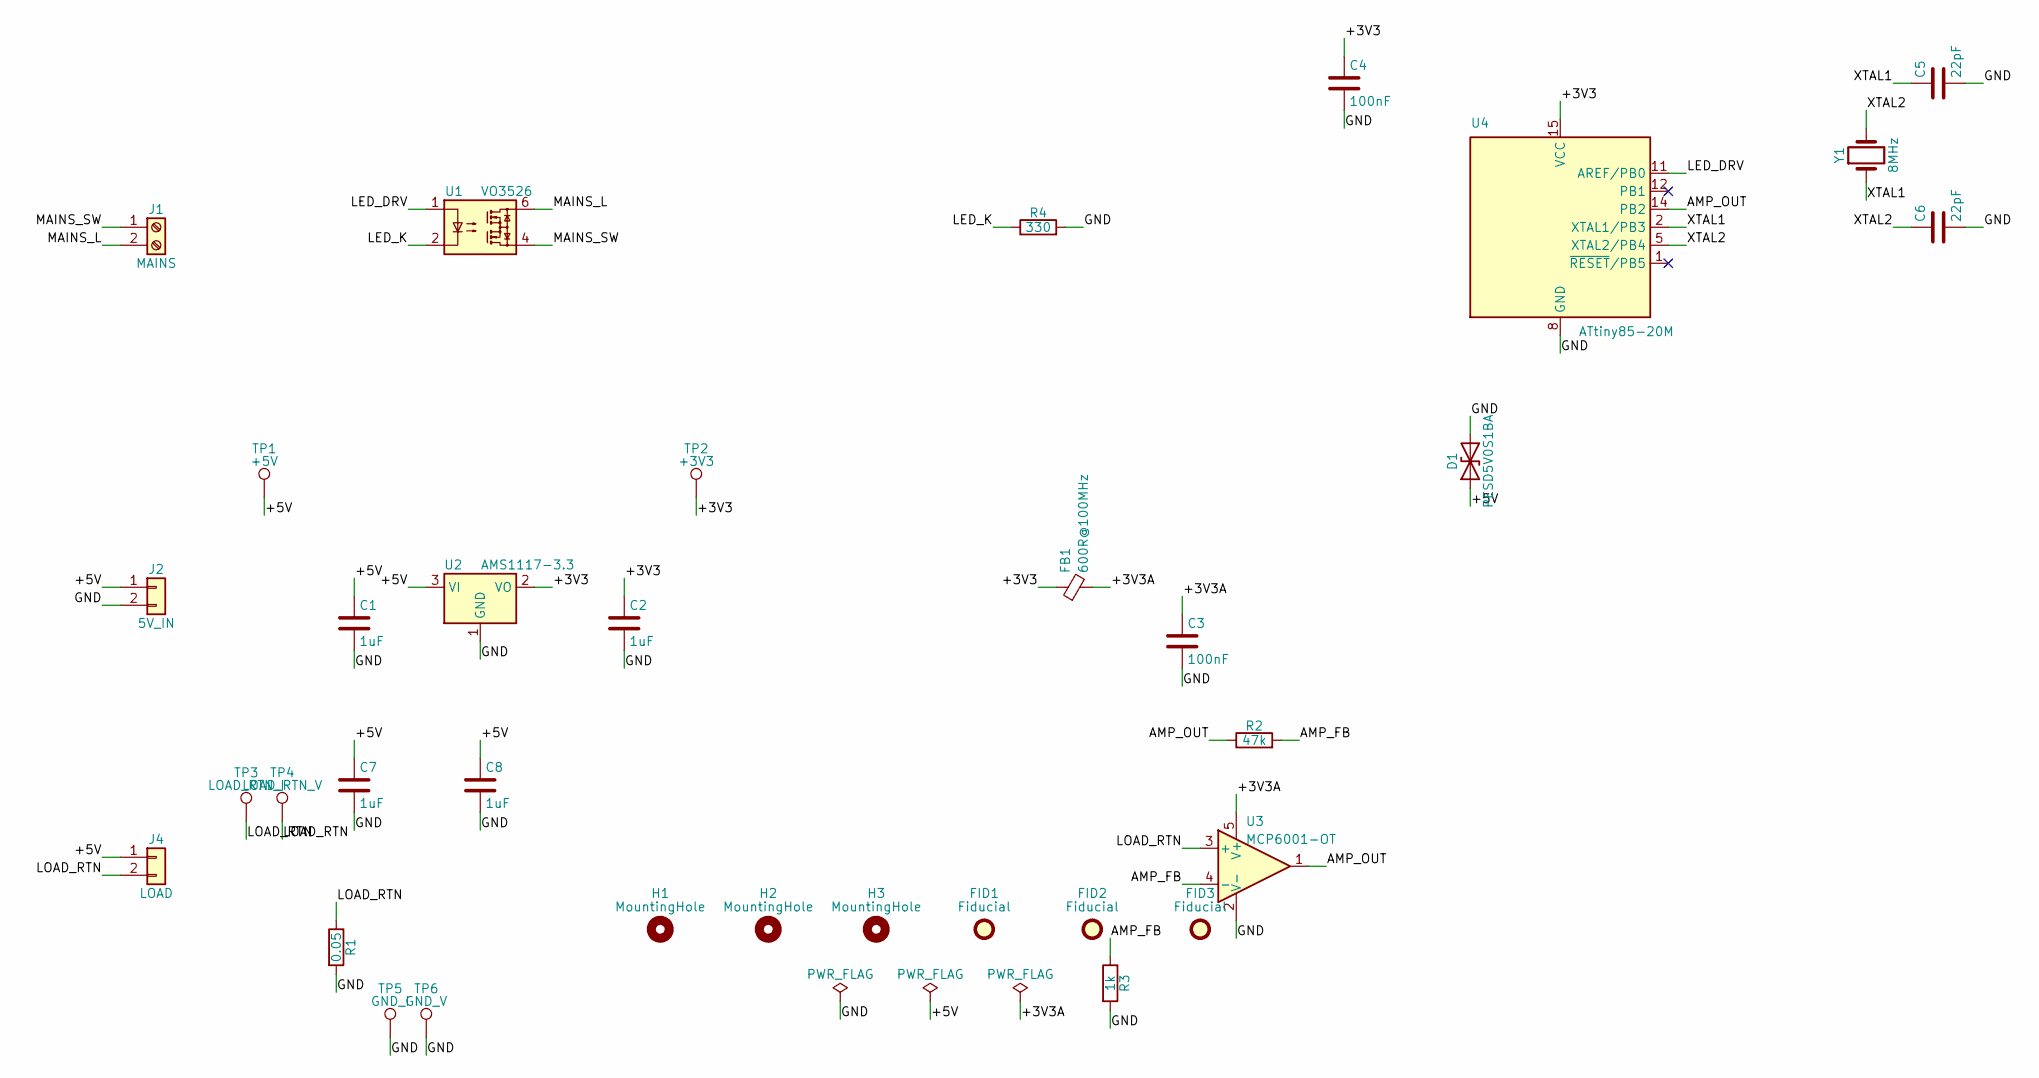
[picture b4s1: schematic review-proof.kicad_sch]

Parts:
C1: 1uF; C_0805_2012Metric; Rating 50V; LCSC C9000004
C2: 1uF; C_0805_2012Metric; Rating 50V; LCSC C9000005
C3: 100nF; C_0603_1608Metric; Rating 50V; LCSC C9000018
C4: 100nF; C_0603_1608Metric; Rating 50V; LCSC C9000020
C5: 22pF; C_0603_1608Metric; Rating 50V; LCSC C9000022
C6: 22pF; C_0603_1608Metric; Rating 50V; LCSC C9000023
C7: 1uF; C_0805_2012Metric; Rating 50V; LCSC C9000027
C8: 1uF; C_0805_2012Metric; Rating 50V; LCSC C9000028
D1: PESD5V0S1BA; D_SOD-323; LCSC C9000025
FB1: 600R@100MHz; L_0603_1608Metric; LCSC C9000017
FID1: Fiducial; Fiducial_1mm_Mask2mm; LCSC C9000032
FID2: Fiducial; Fiducial_1mm_Mask2mm; LCSC C9000033
FID3: Fiducial; Fiducial_1mm_Mask2mm; LCSC C9000034
H1: MountingHole; MountingHole_3.2mm_M3; LCSC C9000029
H2: MountingHole; MountingHole_3.2mm_M3; LCSC C9000030
H3: MountingHole; MountingHole_3.2mm_M3; LCSC C9000031
J1: MAINS; TerminalBlock_Phoenix_MKDS-1,5-2-5.08_1x02_P5.08mm_Horizont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; LCSC C9000001
J2: 5V_IN; JST_XH_B2B-XH-A_1x02_P2.50mm_Vertical; LCSC C9000003
J4: LOAD; JST_XH_B2B-XH-A_1x02_P2.50mm_Vertical; LCSC C9000006
R1: 0.05; R_2512_6332Metric; Rating 0.25W; LCSC C9000007
R2: 47k; R_0603_1608Metric; Rating 0.25W; LCSC C9000015
R3: 1k; R_0603_1608Metric; Rating 0.25W; LCSC C9000016
R4: 330; R_0603_1608Metric; Rating 0.25W; LCSC C9000024
TP1: +5V; TestPoint_Pad_D1.0mm; LCSC C9000008
TP2: +3V3; TestPoint_Pad_D1.0mm; LCSC C9000009
TP3: LOAD_RTN_I; TestPoint_Pad_D1.0mm; LCSC C9000010
TP4: LOAD_RTN_V; TestPoint_Pad_D1.0mm; LCSC C9000011
TP5: GND_I; TestPoint_Pad_D1.0mm; LCSC C9000012
TP6: GND_V; TestPoint_Pad_D1.0mm; LCSC C9000013
U1: VO3526; DIP-5-6_W7.62mm; LCSC C9000002
U2: AMS1117-3.3; SOT-223-3_TabPin2; LCSC C9000026
U3: MCP6001-OT; SOT-23-5; LCSC C9000014
U4: ATtiny85-20M; QFN-20-1EP_4x4mm_P0.5mm_EP2.6x2.6mm; LCSC C9000019
Y1: 8MHz; Crystal_SMD_5032-2Pin_5.0x3.2mm; LCSC C9000021

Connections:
/+3V3: C2.1, C4.1, FB1.1, TP2.1, U2.2 (VO), U4.15 (VCC)
/+3V3A: C3.1, FB1.2, U3.5 (V+)
/+5V: C1.1, C7.1, C8.1, D1.1 (A1), J2.1, J4.1, TP1.1, U2.3 (VI)
/AMP_FB: R2.2, R3.1, U3.4 (-)
/AMP_OUT: R2.1, U3.1, U4.14 (PB2)
/GND: C1.2, C2.2, C3.2, C4.2, C5.2, C6.2, C7.2, C8.2, D1.2 (A2), J2.2, R1.2, R3.2, R4.2, TP5.1, TP6.1, U2.1 (GND), U3.2 (V-), U4.8 (GND), U4.21 (GND)
/LED_DRV: U1.1, U4.11 (AREF/PB0)
/LED_K: R4.1, U1.2
/LOAD_RTN: J4.2, R1.1, TP3.1, TP4.1, U3.3 (+)
/MAINS_L: J1.2, U1.6
/MAINS_SW: J1.1, U1.4
/XTAL1: C5.1, U4.2 (XTAL1/PB3), Y1.1
/XTAL2: C6.1, U4.5 (XTAL2/PB4), Y1.2
